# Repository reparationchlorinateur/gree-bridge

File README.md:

# Gree bridge

A small ESP32-S3 board that goes inside a **mini-split indoor unit** and makes it part of your home, from **Home Assistant**, from **Apple Home** (Matter, straight from the board), or both. It runs [Tasmota](https://tasmota.github.io/) plus a few small Berry scripts.

- **IR control, most brands**: the board drives the unit's own IR receiver line and hears the wall remote on it. This works on most units whose IR receiver feeds the control board directly (most do, especially older ones), with any AC brand Tasmota's IR library knows: Gree, Daikin, Mitsubishi, Fujitsu, LG, Samsung, Panasonic, Toshiba, Midea and many more.
- **The unit's real state, Gree**: it also listens to the indoor/outdoor bus, so you see what the unit is really doing (compressor speed and current, outdoor temperature, coil temperatures...). This is decoded and tested on three Gree bus variants: a **Gree GWH12KF** (600 baud), two Gree-built **Willis MGW12KCH15S/I** (2015, newer 1200 baud bus) and another older Gree unit (600 baud, longer frames). Other Gree units probably use one of these (not checked). For other units, the board's Gree tools page and the Claude Skill help record and decode the bus ([adapting to other units](docs/adapting.md)).

> ⚠️ **Read [SAFETY.md](SAFETY.md) before opening a unit.** This board connects to the logic side of the indoor unit's control board, which sits next to mains voltage and a 56 V communication loop. It was built and tested on **two** Gree models (GWH12KF with indoor board GRJ819-A3, and Willis MGW12KCH15S/I, made by Gree, with indoor board 30148875); the IR part has not been tried on other brands yet. You do this at your own risk; it can void your warranty.

## What it does

- **Controls the unit by IR**, without any IR LED: it drives the unit's own IR receiver line (the wall remote keeps working). Uses Tasmota's IR library (protocol `GREE` here; other brands use their own protocol the same way), so modes, setpoint, fan, swing, turbo, display, etc. are all available.
- **Hears the wall remote** on the same line, so Home Assistant / Apple Home learn about remote presses.
- **Reads the indoor/outdoor bus** (600 or 1200 baud depending on the unit, about one frame per second each way) through two high-impedance taps, listen only: room temperature, indoor coil, mode, setpoint, indoor fan, compressor frequency and current, estimated outdoor power, outdoor air and coil temperatures, discharge temperature, link status. So the app shows the **real** state of the unit, even after a missed remote press or a restart.
- **BME280** (temperature, humidity, pressure) on a plug-in breakout, plus an I2C connector for more sensors.
- **Home Assistant**: everything appears by MQTT discovery; a generated package per room adds the IR climate entity (via `tasmota_irhvac`), turbo and display switches, an energy counter for the Energy dashboard, and an automation that keeps the climate in line with the unit's own state.
- **Apple Home without Home Assistant**: Tasmota's Matter thermostat (v.HVAC) over your normal Wi-Fi, kept in sync with the bus by `gree_matter.be`, plus turbo, display, fan speed, dry mode and swing tiles, the BME280 temperature and humidity and the outdoor temperature; one command (`GreeMatter <room>`) sets it up with the room in every name. Siri, Home app scenes and remote access through a home hub. Other Matter apps (Google Home, Alexa, SmartThings) should work too (not tested).
- **Other units and brands**: a "Gree tools" page detects the wall remote's IR brand, measures the bus speed, format and polarity, and records short captures for decoding; a Claude Skill in this repository walks you through it and decodes the captures ([docs/adapting.md](docs/adapting.md)).
- Wi-Fi recovery hotspot (press BOOT 6 times), OTA updates from the web page.

## What's in this repository

| Folder | Contents |
|---|---|
| [`hardware/`](hardware/) | KiCad 7 project (opens in 7, 8, 9), schematic PDF, assembly sheet (part directions), Gerbers, combined BOM (Mouser + LCSC numbers), JLCPCB assembly files |
| [`hardware/case/`](hardware/case/) | 3D-printable case (PETG, no supports, snap-fit lid): STL, STEP, OpenSCAD source, fit check. Not printed yet |
| [`firmware/`](firmware/) | Tasmota build settings and prebuilt binaries (ESP32-S3), Berry scripts `gree_bus.be` and `gree_matter.be`, GPIO template, host tests |
| [`homeassistant/`](homeassistant/) | Room package generator (`new_room.sh`), package template, example dashboard card |
| [`docs/`](docs/) | [Install guide](docs/install.md) (also without Home Assistant), [hardware description](docs/hardware.md), [bus protocol notes](docs/protocol.md), [adapting to other units](docs/adapting.md), [ordering assembled boards from JLCPCB](docs/order-jlcpcb.md), interactive board viewer |
| [`.claude/skills/gree-bridge/`](.claude/skills/gree-bridge/), [`skill/`](skill/) | Claude Skill: install help, adapting to other units, capture analysis script ([how to add it](skill/README.md)) |

## Quick start

1. **Get a board**: order it assembled from JLCPCB with the files in [`hardware/jlcpcb/`](hardware/jlcpcb/) ([how](docs/order-jlcpcb.md)) (boards assembled from these files are verified working), or order bare PCBs and solder the parts in [`hardware/bom.csv`](hardware/bom.csv) ([assembly sheet](hardware/gree_bridge_revB_assembly_sheet.pdf)). Add the connectors and a GY-BME280 breakout.
2. **Flash** [`firmware/build/gree_tasmota32s3_15.6.0.factory.bin`](firmware/build/) through the J5 header with a 3.3 V USB-serial adapter, from Chrome.
3. **Configure**: Wi-Fi, names, the GPIO template, upload the three scripts.
4. **Install** in the indoor unit (5-wire cable to J1, [where each wire goes](docs/images/gree_board_taps.jpg)), with the breaker off, ideally in the [printed case](hardware/case/).
5. **Connect** to Home Assistant (MQTT + a generated package) and/or pair with Apple Home.

Every step, with the exact console lines: **[docs/install.md](docs/install.md)**.

## Status and compatibility

- Rev B hardware, firmware working since October 2026 on a Gree **GWH12KF** (inverter, R410A, about 2013) with indoor board **GRJ819-A3 / 301484411**: IR both ways, both bus taps, Home Assistant, Apple Home (Matter).
- Since November 2026 also on two **Willis MGW12KCH15S/I** (made by Gree, 2015) with indoor board **30148875** (M836F2UBJ V1.3): a newer bus (1200 baud, 20-byte frames, sum checksum) decoded into the same values, IR (`GREE`) both ways, Home Assistant. [Label, board photo and frame layout](docs/protocol.md#protocol-b-newer-gree-units-1200-baud).
- Also on another older Gree unit with a third bus variant (600 baud, 20- and 29-byte frames, same checksum as the GWH12KF): [protocol C](docs/protocol.md#protocol-c-600-baud-long-frames).
- Other Gree units that use one of these indoor/outdoor loops and a demodulated IR receiver line will probably work, but the tap points differ from board to board. The bus decoder only accepts frames with a valid checksum and finds the tap polarity by itself (`BusAuto`), so a wrong guess is harmless, but measure before you solder (see [SAFETY.md](SAFETY.md) and [docs/protocol.md](docs/protocol.md)).
- Not affiliated with or endorsed by Gree. "Gree" is used only to say which units this is for.

## Licences

- Software (Berry scripts, Home Assistant files, tests, shell and Python scripts, including the Skill's analysis script): [MIT](LICENSE).
- Hardware (KiCad files, Gerbers, BOM) and documentation: [CC BY-SA 4.0](hardware/LICENSE.md).
- The prebuilt firmware is Tasmota (GPL-3.0) built with [`user_config_override.h`](firmware/build/user_config_override.h); see [`firmware/build/README.md`](firmware/build/README.md).

Built on the work of the Tasmota project (Theo Arends, Stephan Hadinger and contributors), IRremoteESP8266, Berry, and the `tasmota_irhvac` Home Assistant integration.

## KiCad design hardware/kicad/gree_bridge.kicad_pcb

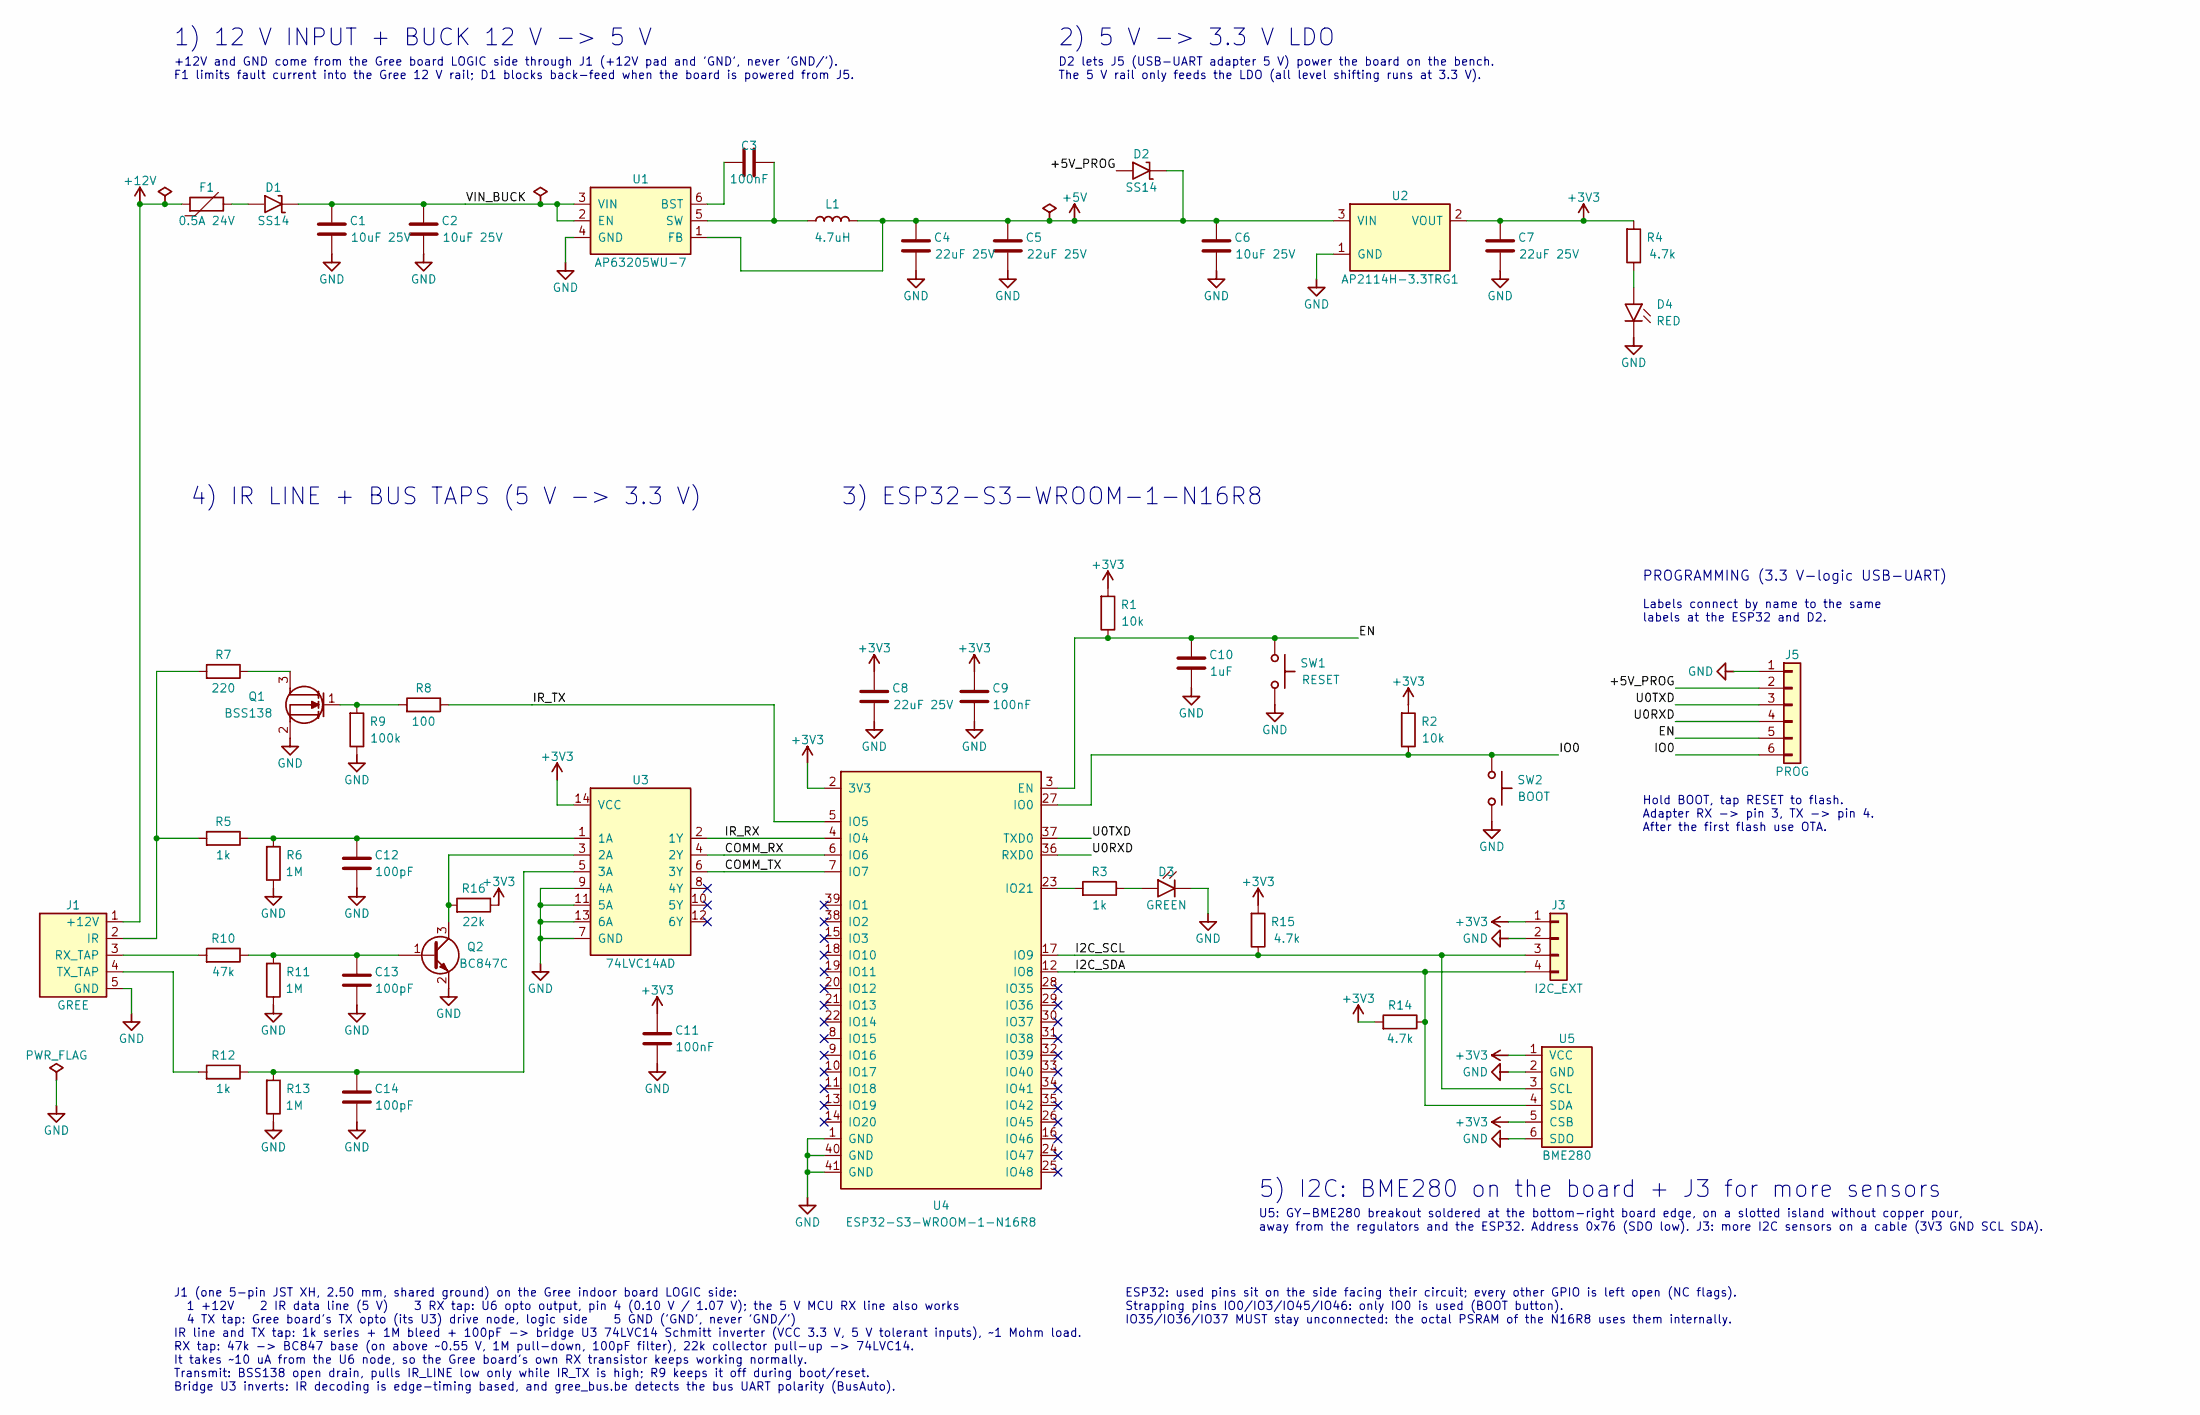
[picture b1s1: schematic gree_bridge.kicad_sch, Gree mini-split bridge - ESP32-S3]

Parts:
C1, C2, C6: 10uF 25V; C_1206_3216Metric_Pad1.33x1.80mm_HandSolder; MPN CC1206KKX7R8BB106; Mouser 603-CC126KKX7R8BB106
C3, C9, C11: 100nF; C_0805_2012Metric_Pad1.18x1.45mm_HandSolder; MPN CC0805KRX7R9BB104; Mouser 603-CC805KRX7R9BB104
C4, C5, C7, C8: 22uF 25V; C_1206_3216Metric_Pad1.33x1.80mm_HandSolder; MPN C3216X5R1E226M160AB; Mouser 810-C3216X5R1E226M
C10: 1uF; C_0805_2012Metric_Pad1.18x1.45mm_HandSolder; MPN CC0805KKX7R8BB105; Mouser 603-CC805KKX7R8BB105
C12, C13, C14: 100pF; C_0805_2012Metric_Pad1.18x1.45mm_HandSolder; MPN CC0805JRNPO9BN101; Mouser 603-CC805JRNPO9BN101
D1, D2: SS14; D_SMA_Handsoldering; MPN SS14; Mouser 512-SS14
D3: GREEN; LED_1206_3216Metric_Pad1.42x1.75mm_HandSolder; MPN LTST-C150KGKT; Mouser 859-LTST-C150KGKT
D4: RED; LED_1206_3216Metric_Pad1.42x1.75mm_HandSolder; MPN LTST-C150KRKT; Mouser 859-LTST-C150KRKT
F1: 0.5A 24V; Fuse_1206_3216Metric_Pad1.42x1.75mm_HandSolder; MPN 0ZCJ0050AF2E; Mouser 530-0ZCJ0050AF2E
J1: GREE; JST_XH_B5B-XH-A_1x05_P2.50mm_Vertical; MPN B5B-XH-A(LF)(SN); Mouser 306-B5BXHALFSN
J3: I2C_EXT; JST_XH_B4B-XH-A_1x04_P2.50mm_Vertical; MPN B4B-XH-A(LF)(SN); Mouser 306-B4BXHALFSN
J5: PROG; PinHeader_1x06_P2.54mm_Vertical; MPN 61300611121; Mouser 710-61300611121
L1: 4.7uH; L_Bourns_SRN6045TA; MPN VLS6045EX-4R7M; Mouser 810-VLS6045EX-4R7M
Q1: BSS138; SOT-23; MPN BSS138; Mouser 512-BSS138
Q2: BC847C; SOT-23; MPN BC847CLT1G; Mouser 863-BC847CLT1G
R1, R2: 10k; R_0805_2012Metric_Pad1.20x1.40mm_HandSolder; MPN RC0805FR-0710KL; Mouser 603-RC0805FR-0710KL
R3, R5, R12: 1k; R_0805_2012Metric_Pad1.20x1.40mm_HandSolder; MPN RC0805FR-071KL; Mouser 603-RC0805FR-071KL
R4, R14, R15: 4.7k; R_0805_2012Metric_Pad1.20x1.40mm_HandSolder; MPN RC0805FR-074K7L; Mouser 603-RC0805FR-074K7L
R6, R11, R13: 1M; R_0805_2012Metric_Pad1.20x1.40mm_HandSolder; MPN RC0805FR-071ML; Mouser 603-RC0805FR-071ML
R7: 220; R_0805_2012Metric_Pad1.20x1.40mm_HandSolder; MPN RC0805FR-07220RL; Mouser 603-RC0805FR-07220RL
R8: 100; R_0805_2012Metric_Pad1.20x1.40mm_HandSolder; MPN RC0805FR-07100RL; Mouser 603-RC0805FR-07100RL
R9: 100k; R_0805_2012Metric_Pad1.20x1.40mm_HandSolder; MPN RC0805FR-07100KL; Mouser 603-RC0805FR-07100KL
R10: 47k; R_0805_2012Metric_Pad1.20x1.40mm_HandSolder; MPN RC0805FR-0747KL; Mouser 603-RC0805FR-0747KL
R16: 22k; R_0805_2012Metric_Pad1.20x1.40mm_HandSolder; MPN RC0805FR-0722KL; Mouser 603-RC0805FR-0722KL
SW1: RESET; SW_SPST_PTS645; MPN PTS645SL43SMTR92 LFS; Mouser 611-PTS645SL43SMTR92
SW2: BOOT; SW_SPST_PTS645; MPN PTS645SL43SMTR92 LFS; Mouser 611-PTS645SL43SMTR92
U1: AP63205WU-7; TSOT-23-6; MPN AP63205WU-7; Mouser 621-AP63205WU-7
U2: AP2114H-3.3TRG1; SOT-223-3_TabPin2; MPN AP2114H-3.3TRG1; Mouser 621-AP2114H-3.3TRG1
U3: 74LVC14AD; SOIC-14_3.9x8.7mm_P1.27mm; MPN SN74LVC14ADRG4; Mouser 595-SN74LVC14ADRG4
U4: ESP32-S3-WROOM-1-N16R8; ESP32-S3-WROOM-1; MPN ESP32-S3-WROOM-1-N16R8; Mouser 356-ESP32S3WRM1N16R8
U5: BME280; BME280_Module_GY_1x06_P2.54mm; MPN GY-BME280 6-pin breakout

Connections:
+3V3: C7.1, C8.1, C9.1, C11.1, J3.1, R1.1, R2.1, R4.1, R14.1, R15.1, R16.2, U2.2 (VOUT), U3.14 (VCC), U4.2 (3V3), U5.1 (VCC), U5.5 (CSB)
+5V: C4.1, C5.1, C6.1, D2.1 (K), L1.2, U1.1 (FB), U2.3 (VIN)
+12V: F1.1, J1.1 (+12V)
/+5V_PROG: D2.2 (A), J5.2
/COMM_RX: U3.4 (2Y), U4.6 (IO6)
/COMM_TX: U3.6 (3Y), U4.7 (IO7)
/EN: C10.1, J5.5, R1.2, SW1.1, U4.3 (EN)
/I2C_SCL: J3.3, R15.2, U4.17 (IO9), U5.3 (SCL)
/I2C_SDA: J3.4, R14.2, U4.12 (IO8), U5.4 (SDA)
/IO0: J5.6, R2.2, SW2.1, U4.27 (IO0)
/IR_RX: U3.2 (1Y), U4.4 (IO4)
/IR_TX: R8.2, U4.5 (IO5)
/U0RXD: J5.4, U4.36 (RXD0)
/U0TXD: J5.3, U4.37 (TXD0)
/VIN_BUCK: C1.1, C2.1, D1.1 (K), U1.2 (EN), U1.3 (VIN)
GND: C1.2, C2.2, C4.2, C5.2, C6.2, C7.2, C8.2, C9.2, C10.2, C11.2, C12.2, C13.2, C14.2, D3.1 (K), D4.1 (K), J1.5 (GND), J3.2, J5.1, Q1.2 (S), Q2.2 (E), R6.2, R9.2, R11.2, R13.2, SW1.2, SW2.2, U1.4 (GND), U2.1 (GND), U3.7 (GND), U3.9 (4A), U3.11 (5A), U3.13 (6A), U4.1 (GND), U4.40 (GND), U4.41 (GND), U5.2 (GND), U5.6 (SDO)
unnamed: D1.2 (A), F1.2
unnamed: D3.2 (A), R3.2
unnamed: D4.2 (A), R4.2
unnamed: J1.2 (IR), R5.1, R7.1
unnamed: J1.3 (RX_TAP), R10.1
unnamed: J1.4 (TX_TAP), R12.1
unnamed: Q1.3 (D), R7.2
unnamed: Q1.1 (G), R8.1, R9.1
unnamed: C13.1, Q2.1 (B), R10.2, R11.1
unnamed: Q2.3 (C), R16.1, U3.3 (2A)
unnamed: C3.1, U1.6 (BST)
unnamed: C3.2, L1.1, U1.5 (SW)
unnamed: C12.1, R5.2, R6.1, U3.1 (1A)
unnamed: C14.1, R12.2, R13.1, U3.5 (3A)
unnamed: R3.1, U4.23 (IO21)

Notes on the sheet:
1) 12 V INPUT + BUCK 12 V -> 5 V
+12V and GND come from the Gree board LOGIC side through J1 (+12V pad and 'GND', never 'GND/'). F1 limits fault current into the Gree 12 V rail; D1 blocks back-feed when the board is powered from J5.
2) 5 V -> 3.3 V LDO
D2 lets J5 (USB-UART adapter 5 V) power the board on the bench. The 5 V rail only feeds the LDO (all level shifting runs at 3.3 V).
4) IR LINE + BUS TAPS (5 V -> 3.3 V)
J1 (one 5-pin JST XH, 2.50 mm, shared ground) on the Gree indoor board LOGIC side: 1 +12V 2 IR data line (5 V) 3 RX tap: U6 opto output, pin 4 (0.10 V / 1.07 V); the 5 V MCU RX line also works 4 TX tap: Gree board's TX opto (its U3) drive node, logic side 5 GND ('GND', never 'GND/') IR line and TX 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
3) ESP32-S3-WROOM-1-N16R8
ESP32: used pins sit on the side facing their circuit; every other GPIO is left open (NC flags). Strapping pins IO0/IO3/IO45/IO46: only IO0 is used (BOOT button). IO35/IO36/IO37 MUST stay unconnected: the octal PSRAM of the N16R8 uses them internally.
5) I2C: BME280 on the board + J3 for more sensors
U5: GY-BME280 breakout soldered at the bottom-right board edge, on a slotted island without copper pour, away from the regulators and the ESP32. Address 0x76 (SDO low). J3: more I2C sensors on a cable (3V3 GND SCL SDA).
PROGRAMMING (3.3 V-logic USB-UART)
Labels connect by name to the same labels at the ESP32 and D2.
Hold BOOT, tap RESET to flash. Adapter RX -> pin 3, TX -> pin 4. After the first flash use OTA.

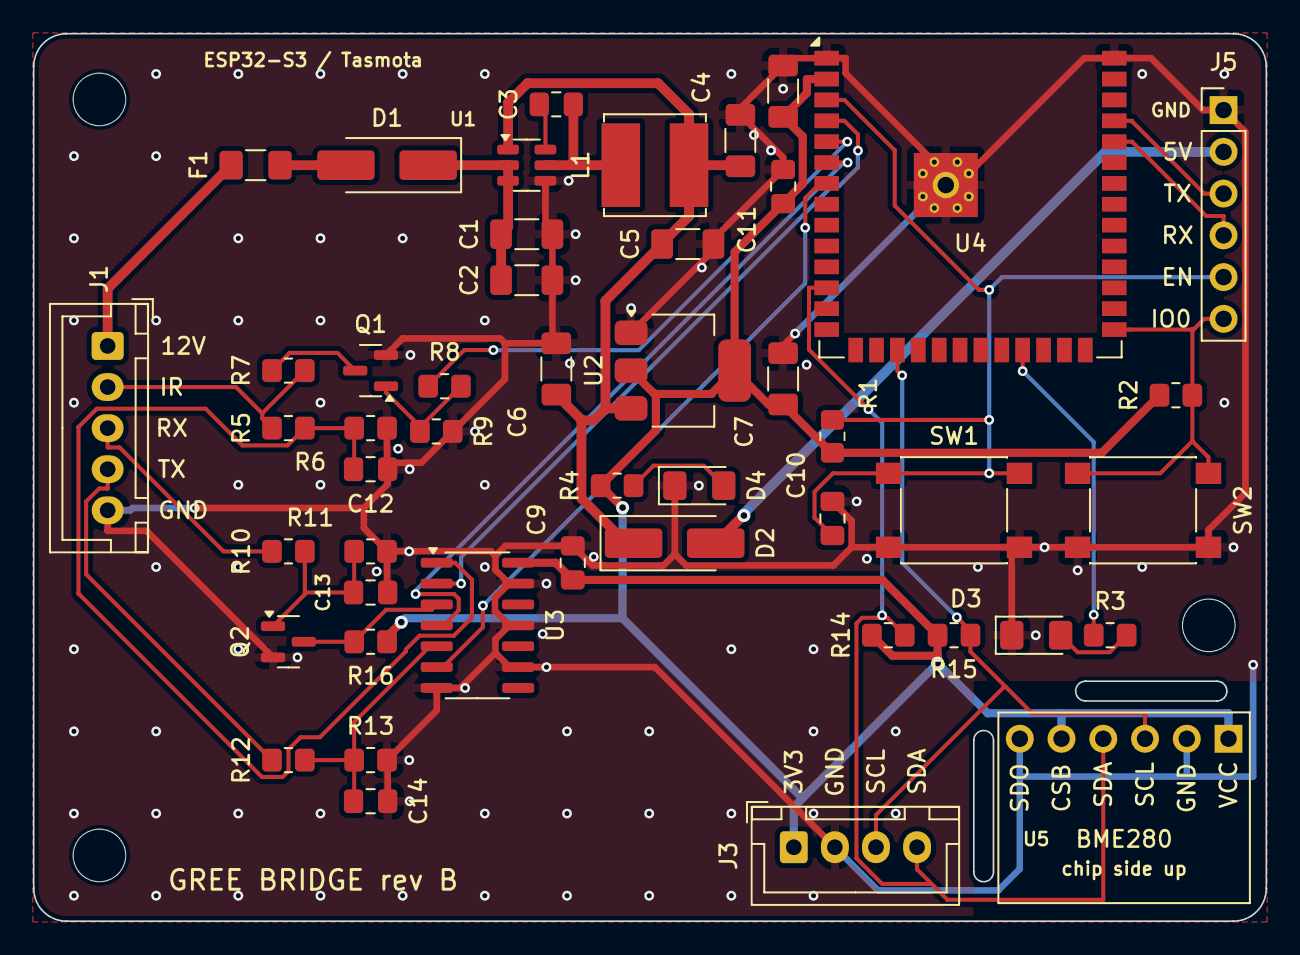
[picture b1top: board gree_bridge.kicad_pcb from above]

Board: 2 copper layers, 75.0 x 54.0 mm, 51 parts (0 on the bottom side), 31 nets.

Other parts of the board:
H1, H2, H3: M3; MountingHole_3.2mm_M3

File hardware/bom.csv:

Line,References,Qty per board,Value,Description,Manufacturer,Mfr part #,Mouser #,LCSC # (JLCPCB),JLCPCB part,KiCad footprint,Notes
1,C1 C2 C6,3,10uF 25V,MLCC 10 uF 25 V X7R 1206,YAGEO,CC1206KKX7R8BB106,603-CC126KKX7R8BB106,C14860,10uF 25V X7R 1206 Samsung CL31B106KAHNNNE [SUBSTITUTE],Capacitor_SMD:C_1206_3216Metric_Pad1.33x1.80mm_HandSolder,
2,C3 C9 C11,3,100nF,MLCC 100 nF 50 V X7R 0805,YAGEO,CC0805KRX7R9BB104,603-CC805KRX7R9BB104,C49678,100nF 50V X7R 0805 YAGEO CC0805KRX7R9BB104,Capacitor_SMD:C_0805_2012Metric_Pad1.18x1.45mm_HandSolder,
3,C4 C5 C7 C8,4,22uF 25V,MLCC 22 uF 25 V X5R 1206,TDK,C3216X5R1E226M160AB,810-C3216X5R1E226M,C12891,22uF 25V X5R 1206 Samsung CL31A226KAHNNNE [SUBSTITUTE],Capacitor_SMD:C_1206_3216Metric_Pad1.33x1.80mm_HandSolder,25 V part keeps more of its capacitance at 5 V than a 10 V one
4,C10,1,1uF,MLCC 1 uF 25 V X7R 0805,YAGEO,CC0805KKX7R8BB105,603-CC805KKX7R8BB105,C28323,1uF 50V X7R 0805 Samsung CL21B105KBFNNNE [SUBSTITUTE],Capacitor_SMD:C_0805_2012Metric_Pad1.18x1.45mm_HandSolder,
5,C12 C13 C14,3,100pF,MLCC 100 pF 50 V C0G 0805,YAGEO,CC0805JRNPO9BN101,603-CC805JRNPO9BN101,C1790,100pF 50V C0G 0805 Samsung CL21C101JBANNNC [SUBSTITUTE],Capacitor_SMD:C_0805_2012Metric_Pad1.18x1.45mm_HandSolder,
6,D1 D2,2,SS14,"Schottky diode 40 V 1 A, SMA",onsemi,SS14,512-SS14,C2480,SS14 40V 1A SMA MDD SS14 [SUBSTITUTE],Diode_SMD:D_SMA_Handsoldering,
7,D3,1,GREEN,"LED green (AlInGaP, 35 mcd), 1206 (status)",Lite-On,LTST-C150KGKT,859-LTST-C150KGKT,C125085,LED green 1206 Lite-On LTST-C150KGKT,LED_SMD:LED_1206_3216Metric_Pad1.42x1.75mm_HandSolder,Brighter AlInGaP green; about 1.5 mA from GPIO21 through R3 (1k)
8,D4,1,RED,"LED red, 1206 (power)",Lite-On,LTST-C150KRKT,859-LTST-C150KRKT,C125086,LED red 1206 Lite-On LTST-C150KRKT,LED_SMD:LED_1206_3216Metric_Pad1.42x1.75mm_HandSolder,
9,F1,1,0.5A 24V,"PTC resettable fuse 0.5 A hold, 24 V max, 1206",Bel Fuse,0ZCJ0050AF2E,530-0ZCJ0050AF2E,C883126,PTC 0.5A hold 1A trip 1206 BHFUSE BSMD1206-050-30V [SUBSTITUTE],Fuse:Fuse_1206_3216Metric_Pad1.42x1.75mm_HandSolder,24 V rated for the 12 V rail (the 6 V 1206L050YR of the first draft was not)
10,J1,1,GREE,"JST XH 5-pin vertical through-hole header, 2.50 mm (to the Gree board)",JST,B5B-XH-A(LF)(SN),306-B5BXHALFSN,C157991,JST XH 5-pin vertical (THT) JST B5B-XH-A(LF)(SN) [THT - hand-solder or JLC THT option],Connector_JST:JST_XH_B5B-XH-A_1x05_P2.50mm_Vertical,
11,J3,1,I2C_EXT,"JST XH 4-pin vertical through-hole header, 2.50 mm (I2C port for more sensors)",JST,B4B-XH-A(LF)(SN),306-B4BXHALFSN,C144395,JST XH 4-pin vertical (THT) JST B4B-XH-A(LF)(SN) [THT - hand-solder or JLC THT option],Connector_JST:JST_XH_B4B-XH-A_1x04_P2.50mm_Vertical,
12,J5,1,PROG,"Pin header 1x6 2.54 mm, straight, through-hole, gold (programming)",Wurth Elektronik,61300611121,710-61300611121,C5444523,Pin header 1x6 2.54mm (THT) Wurth 61300611121 [THT - hand-solder or JLC THT option],Connector_PinHeader_2.54mm:PinHeader_1x06_P2.54mm_Vertical,"Plain straight header (6 mm mating pins, 3 mm solder tails); replaces the alternating-leg SMD header"
13,L1,1,4.7uH,"Inductor 4.7 uH +/-20%, 27 mOhm, Isat 5.8 A, shielded 6 x 6 x 4.5 mm",TDK,VLS6045EX-4R7M,810-VLS6045EX-4R7M,C307880,4.7uH 5.8A 6x6x4.5 TDK VLS6045EX-4R7M,Inductor_SMD:L_Bourns_SRN6045TA,"Replaces Bourns SRN6045TA-4R7M (0 in stock on 2026-10-08); fits the same pads, no PCB change. The Bourns part still fits if you prefer it"
14,Q1,1,BSS138,"N-MOSFET 50 V, SOT-23 (IR transmit)",onsemi,BSS138,512-BSS138,C52895,BSS138 SOT-23 onsemi BSS138,Package_TO_SOT_SMD:SOT-23,
15,Q2,1,BC847C,"NPN 45 V 100 mA, SOT-23, hFE 420-800 (RX level stage)",onsemi,BC847CLT1G,863-BC847CLT1G,C150094,BC847C SOT-23 onsemi BC847CLT1G,Package_TO_SOT_SMD:SOT-23,New in rev B: lets J1-3 take the low-voltage U6 opto output
16,R1 R2,2,10k,Resistor 10k 1% 1/8 W 0805,YAGEO,RC0805FR-0710KL,603-RC0805FR-0710KL,C17414,10k 1% 0805 UNI-ROYAL 0805W8F1002T5E [SUBSTITUTE],Resistor_SMD:R_0805_2012Metric_Pad1.20x1.40mm_HandSolder,
17,R3 R5 R12,3,1k,Resistor 1k 1% 1/8 W 0805,YAGEO,RC0805FR-071KL,603-RC0805FR-071KL,C17513,1k 1% 0805 UNI-ROYAL 0805W8F1001T5E [SUBSTITUTE],Resistor_SMD:R_0805_2012Metric_Pad1.20x1.40mm_HandSolder,
18,R4 R14 R15,3,4.7k,Resistor 4.7k 1% 1/8 W 0805,YAGEO,RC0805FR-074K7L,603-RC0805FR-074K7L,C17673,4.7k 1% 0805 UNI-ROYAL 0805W8F4701T5E [SUBSTITUTE],Resistor_SMD:R_0805_2012Metric_Pad1.20x1.40mm_HandSolder,
19,R6 R11 R13,3,1M,Resistor 1M 1% 1/8 W 0805,YAGEO,RC0805FR-071ML,603-RC0805FR-071ML,C17514,1M 1% 0805 UNI-ROYAL 0805W8F1004T5E [SUBSTITUTE],Resistor_SMD:R_0805_2012Metric_Pad1.20x1.40mm_HandSolder,
20,R7,1,220,Resistor 220 1% 1/8 W 0805,YAGEO,RC0805FR-07220RL,603-RC0805FR-07220RL,C17557,220 1% 0805 UNI-ROYAL 0805W8F2200T5E [SUBSTITUTE],Resistor_SMD:R_0805_2012Metric_Pad1.20x1.40mm_HandSolder,
21,R8,1,100,Resistor 100 1% 1/8 W 0805,YAGEO,RC0805FR-07100RL,603-RC0805FR-07100RL,C17408,100 1% 0805 UNI-ROYAL 0805W8F1000T5E [SUBSTITUTE],Resistor_SMD:R_0805_2012Metric_Pad1.20x1.40mm_HandSolder,
22,R9,1,100k,Resistor 100k 1% 1/8 W 0805,YAGEO,RC0805FR-07100KL,603-RC0805FR-07100KL,C149504,100k 1% 0805 UNI-ROYAL 0805W8F1003T5E [SUBSTITUTE],Resistor_SMD:R_0805_2012Metric_Pad1.20x1.40mm_HandSolder,
23,R10,1,47k,Resistor 47k 1% 1/8 W 0805,YAGEO,RC0805FR-0747KL,603-RC0805FR-0747KL,C17713,47k 1% 0805 UNI-ROYAL 0805W8F4702T5E [SUBSTITUTE],Resistor_SMD:R_0805_2012Metric_Pad1.20x1.40mm_HandSolder,R10 is 47k now (was 1k): base resistor of Q2
24,R16,1,22k,Resistor 22k 1% 1/8 W 0805,YAGEO,RC0805FR-0722KL,603-RC0805FR-0722KL,C17560,22k 1% 0805 UNI-ROYAL 0805W8F2202T5E [SUBSTITUTE],Resistor_SMD:R_0805_2012Metric_Pad1.20x1.40mm_HandSolder,R16: Q2 collector pull-up
25,SW1 SW2,2,RESET / BOOT,"Tact switch 6 x 6 mm SMD gull-wing, 4.3 mm, 1.3 N",C&K,PTS645SL43SMTR92 LFS,611-PTS645SL43SMTR92,C221880,Tact 6x6 SMD 4.3mm C&K PTS645SM43SMTR92LFS [SUBSTITUTE],Button_Switch_SMD:SW_SPST_PTS645,"SL = 1.3 N version of the PTS645SM43 (1.6 N, restricted availability); same footprint"
26,U1,1,AP63205WU-7,"Buck regulator 5 V 2 A, TSOT-23-6",Diodes Incorporated,AP63205WU-7,621-AP63205WU-7,C2071056,AP63205WU-7 buck 5V 2A Diodes Inc AP63205WU-7,Package_TO_SOT_SMD:TSOT-23-6,
27,U2,1,AP2114H-3.3TRG1,"LDO 3.3 V 1 A, SOT-223",Diodes Incorporated,AP2114H-3.3TRG1,621-AP2114H-3.3TRG1,C150716,AP2114H-3.3TRG1 LDO Diodes Inc AP2114H-3.3TRG1,Package_TO_SOT_SMD:SOT-223-3_TabPin2,
28,U3,1,74LVC14AD,"Hex Schmitt-trigger inverter, SOIC-14",Texas Instruments,SN74LVC14ADRG4,595-SN74LVC14ADRG4,C133541,SN74LVC14A SOIC-14 TI SN74LVC14ADR [ORDERABLE VARIANT],Package_SO:SOIC-14_3.9x8.7mm_P1.27mm,Same TI part as SN74LVC14ADR (G4 = green package code); the plain ADR was on order only
29,U4,1,ESP32-S3-WROOM-1-N16R8,"ESP32-S3 module, 16 MB flash, 8 MB PSRAM",Espressif,ESP32-S3-WROOM-1-N16R8,356-ESP32S3WRM1N16R8,C2913202,ESP32-S3-WROOM-1-N16R8 Espressif ESP32-S3-WROOM-1-N16R8,RF_Module:ESP32-S3-WROOM-1,
30,U5,1,GY-BME280,"BME280 breakout module, 6-pin (VCC GND SCL SDA CSB SDO), 3.3 V version",generic,GY-BME280,,,,GreeBridge:BME280_Module_GY_1x06_P2.54mm,"Not a JLCPCB part: plug-in breakout on a 1x6 header, chip side up; address 0x76"
